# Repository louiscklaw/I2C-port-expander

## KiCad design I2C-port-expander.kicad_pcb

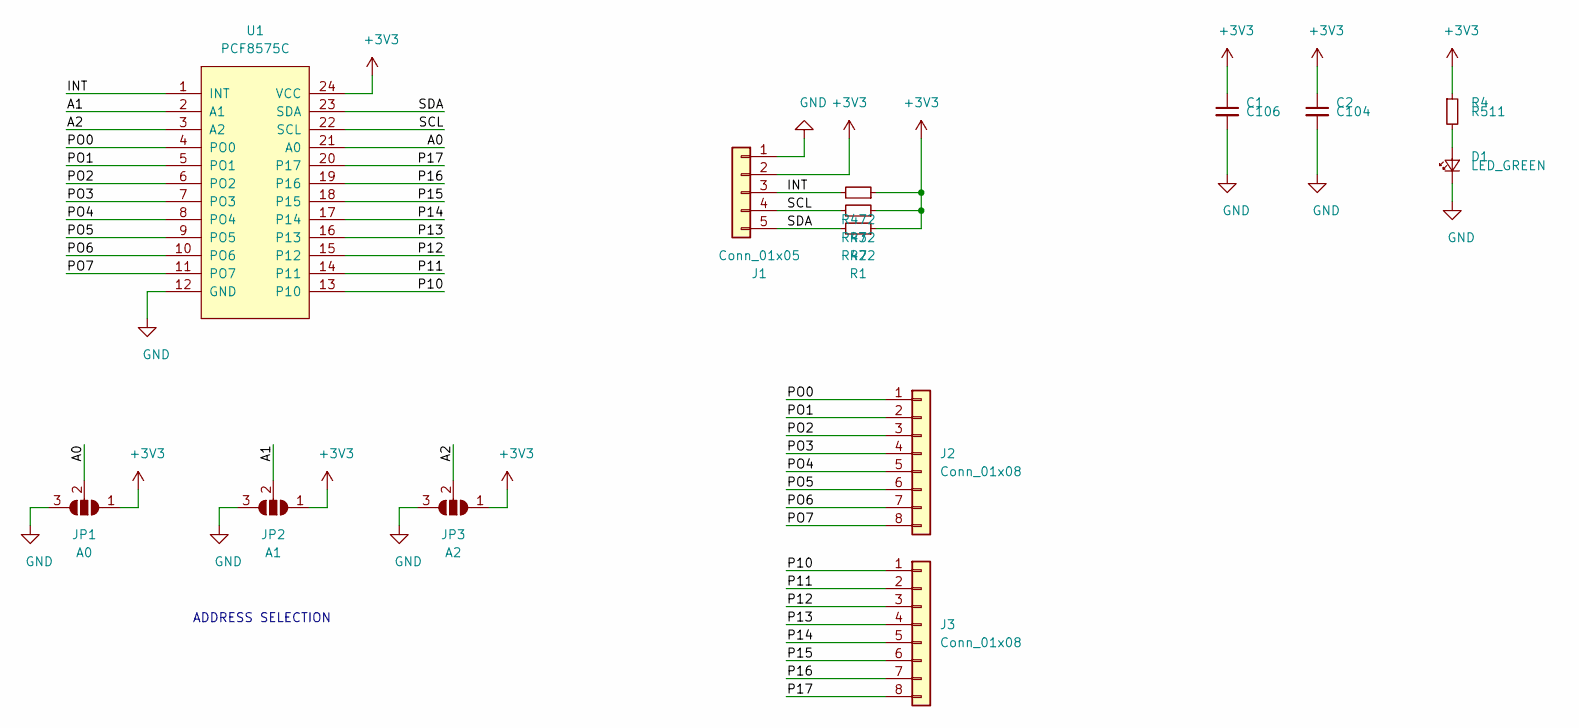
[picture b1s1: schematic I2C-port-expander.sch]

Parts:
C1: C106; C_0805_2012Metric_Pad1.15x1.40mm_HandSolder
C2: C104; C_0805_2012Metric_Pad1.15x1.40mm_HandSolder
D1: LED_GREEN; LED_0805_2012Metric_Castellated
J1: Conn_01x05; PinHeader_1x05_P2.54mm_Vertical
J2, J3: Conn_01x08; PinHeader_1x08_P2.54mm_Vertical
JP1: A0; SolderJumper-3_P1.3mm_Open_RoundedPad1.0x1.5mm_NumberLabels
JP2: A1; SolderJumper-3_P1.3mm_Open_RoundedPad1.0x1.5mm_NumberLabels
JP3: A2; SolderJumper-3_P1.3mm_Open_RoundedPad1.0x1.5mm_NumberLabels
R1, R2, R3: R472; R_0805_2012Metric_Pad1.15x1.40mm_HandSolder
R4: R511; R_0805_2012Metric_Pad1.15x1.40mm_HandSolder
U1: PCF8575C; SSOP-24_5.3x8.2mm_P0.65mm

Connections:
+3V3: C1.1, C2.1, J1.2, JP1.1 (A), JP2.1 (A), JP3.1 (A), R1.1, R2.1, R3.1, R4.1, U1.24 (VCC)
/A0: JP1.2 (C), U1.21 (A0)
/A1: JP2.2 (C), U1.2 (A1)
/A2: JP3.2 (C), U1.3 (A2)
/INT: J1.3, R3.2, U1.1 (INT)
/P10: J3.1, U1.13 (P10)
/P11: J3.2, U1.14 (P11)
/P12: J3.3, U1.15 (P12)
/P13: J3.4, U1.16 (P13)
/P14: J3.5, U1.17 (P14)
/P15: J3.6, U1.18 (P15)
/P16: J3.7, U1.19 (P16)
/P17: J3.8, U1.20 (P17)
/PO0: J2.1, U1.4 (PO0)
/PO1: J2.2, U1.5 (PO1)
/PO2: J2.3, U1.6 (PO2)
/PO3: J2.4, U1.7 (PO3)
/PO4: J2.5, U1.8 (PO4)
/PO5: J2.6, U1.9 (PO5)
/PO6: J2.7, U1.10 (PO6)
/PO7: J2.8, U1.11 (PO7)
/SCL: J1.4, R2.2, U1.22 (SCL)
/SDA: J1.5, R1.2, U1.23 (SDA)
GND: C1.2, C2.2, D1.1 (K), J1.1, JP1.3 (B), JP2.3 (B), JP3.3 (B), U1.12 (GND)
unnamed: D1.2 (A), R4.2

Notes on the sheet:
ADDRESS SELECTION

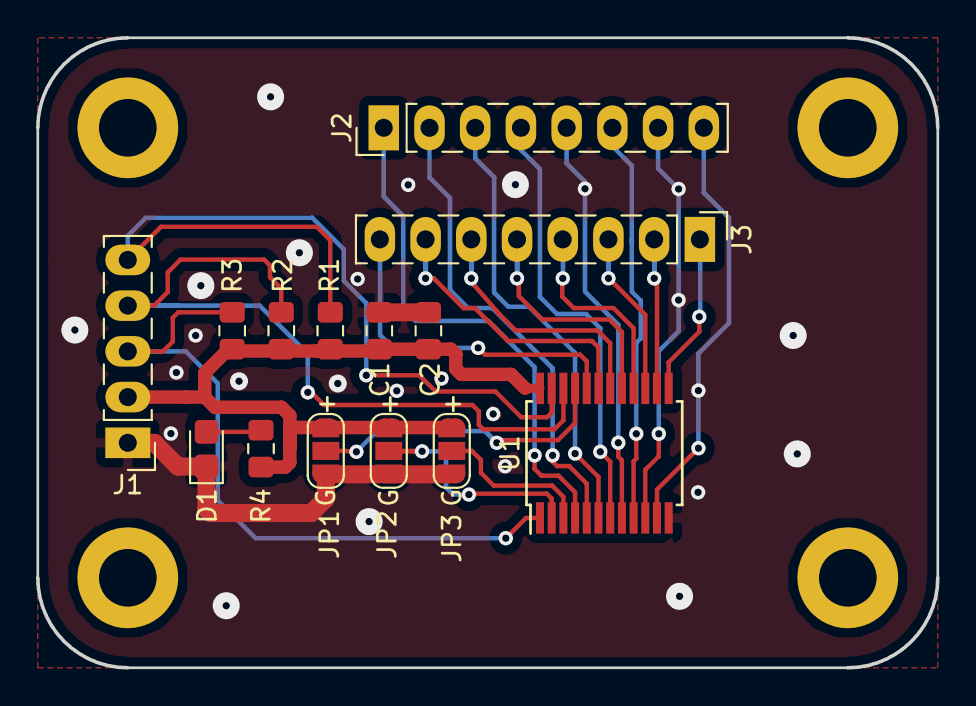
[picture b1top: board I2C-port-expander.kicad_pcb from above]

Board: 2 copper layers, 50.0 x 35.0 mm, 14 parts (0 on the bottom side), 25 nets.

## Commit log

2018-10-17 update,
2018-10-17 update jumper marking,
2020-05-05 ci: init travis build config,
2020-05-05 ci: init travis token,
